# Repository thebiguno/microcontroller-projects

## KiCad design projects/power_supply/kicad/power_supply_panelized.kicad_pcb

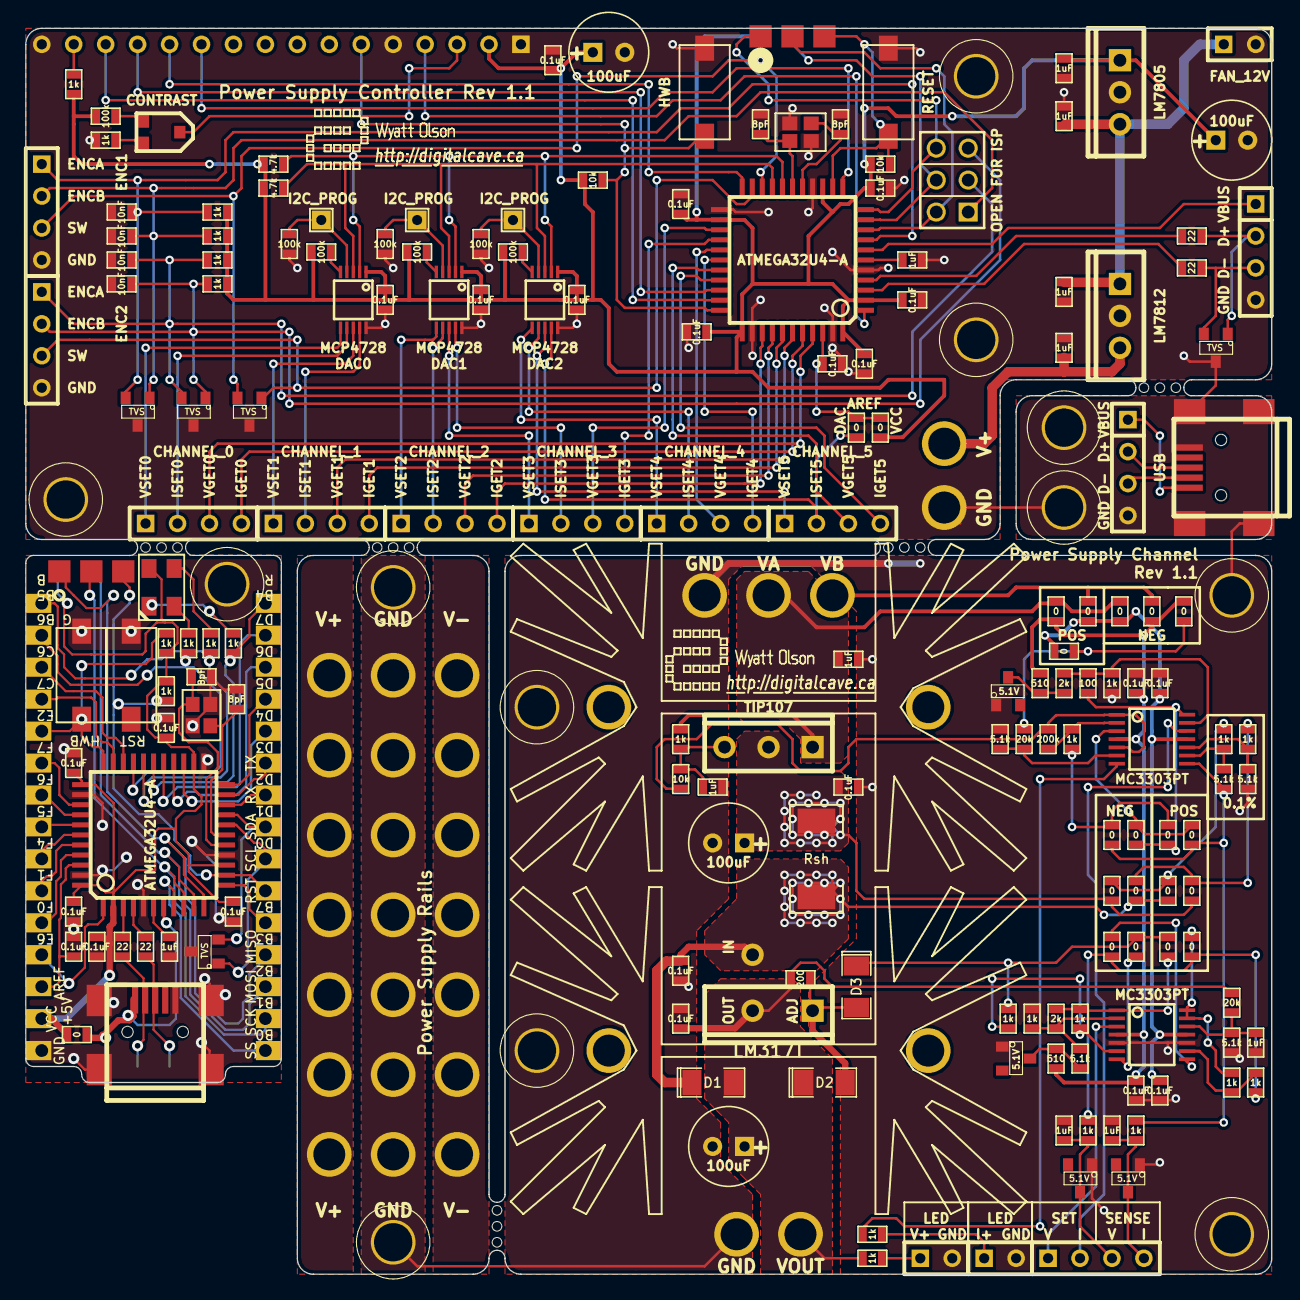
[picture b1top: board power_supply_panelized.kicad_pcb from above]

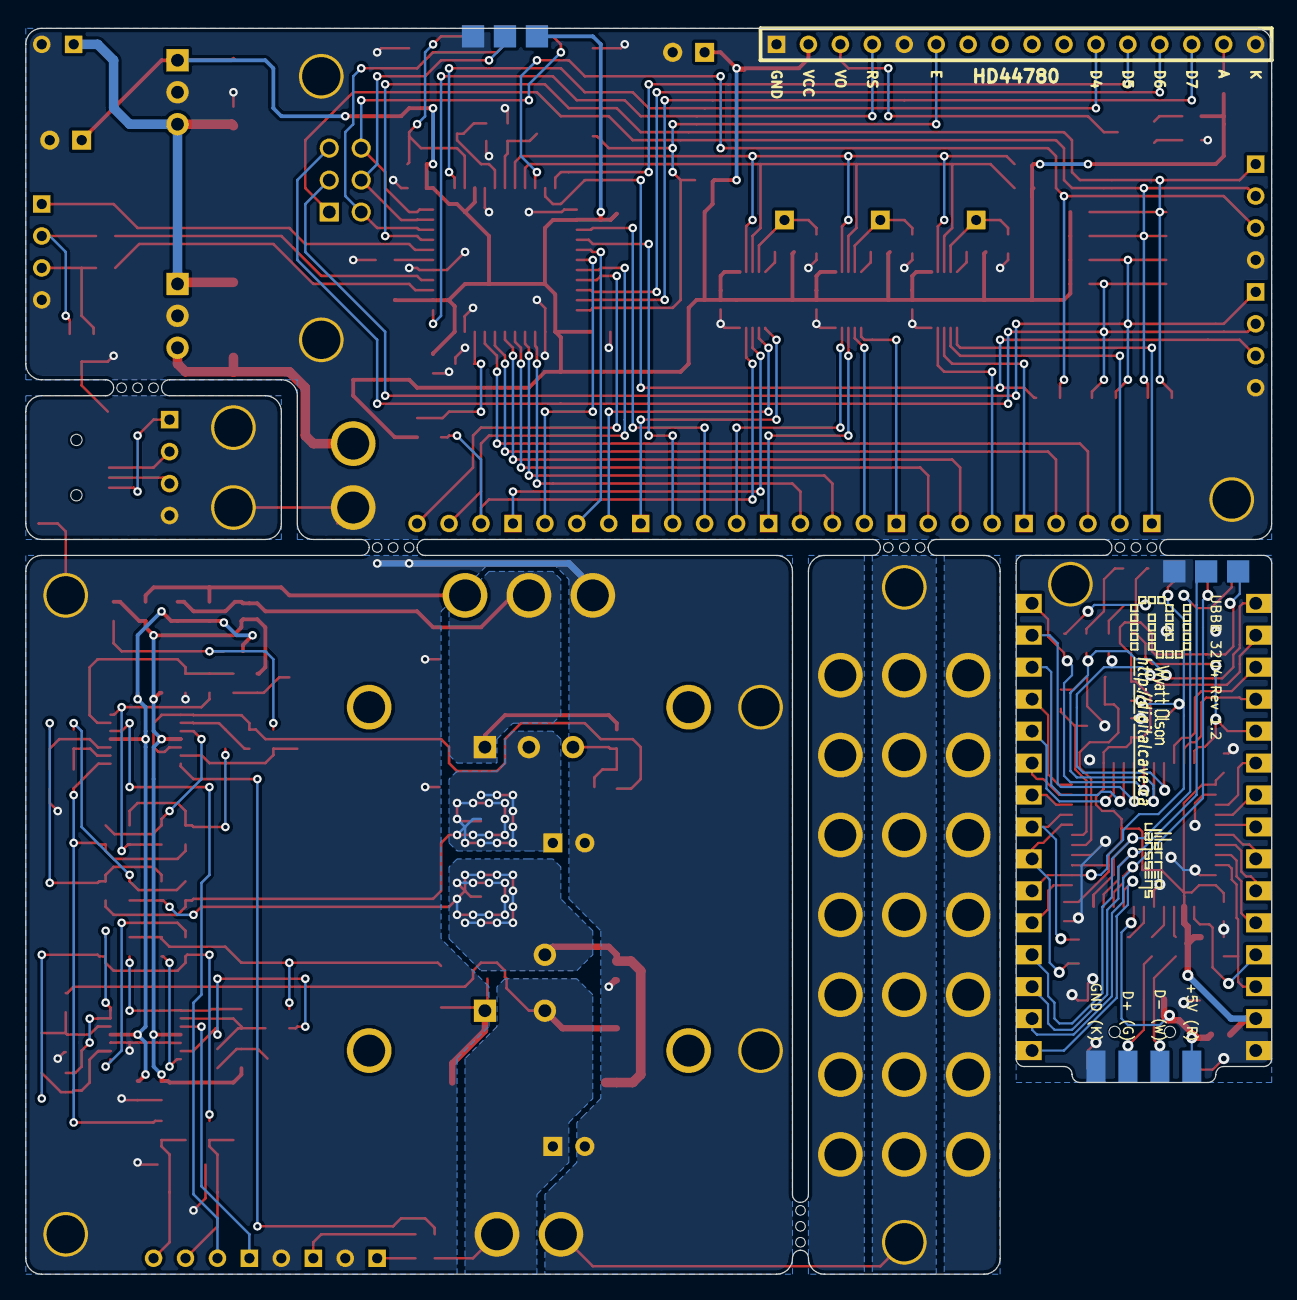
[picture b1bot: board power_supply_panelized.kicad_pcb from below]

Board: 2 copper layers, 99.1 x 99.1 mm, 223 parts (6 on the bottom side), 140 nets.

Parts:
C1, C2, C3, C4: 100uF; C1V7
C1#2, C2#2, C23, C26: 8pF; SM0603_VALUE
C3#2, C5, C5#2, C6, C6#2, C7, C7#2, C8, C8#2, C9, C9#2, C11, C12, C17, C18, C19, C20, C21, C22, C34, C35, C36, C37: 0.1uF; SM0603_VALUE
C4#2, C10, C13, C14, C15, C16, C24, C25, C31, C32, C33: 1uF; SM0603_VALUE
C27, C28, C29, C30: 10nF; SM0603_VALUE
CON1, CON1#2: USB-MINI-B; USB_MINI_B_fixed
D1, D2, D3: SCHOTTKEY; SM1206_DIODE
D1#2: RGB_LED_COMMON_ANODE_ALT1; LED_RGB_4-PLCC_ALT1
D2#2, D8, D9, D10, D11: TVS; SOT23
D4, D5, D6, D7: 5.1V; SOT23-SPECIAL
DIGITALCAVE_URL: VAL**; DIGITALCAVE_URL
DS1: HD44780; SIL-16
K1, K2, K3, K4, K5, K6, K7: VS; SCREW_TERMINAL_3
K1#2: PINS_4; PIN_ARRAY_4x1
K8: V_LED; SIL-2
K9: SUPPLY; SCREW_TERMINAL_3
K10: VOUT; SCREW_TERMINAL_2
K11: CONTROL_FEEDBACK; SIL-4
K12, K14: HEATSINK; HEATSINK_OHMITE_FSERIES
K13: I_LIM_LED; SIL-2
K15, K17: USB; SIL-4
K16: POWER; SCREW_TERMINAL_2
K18: ENC1; SIL-4
K19: ENC2; SIL-4
K20: FAN_12V; SIL-2
K21, K22, K23: I2C_PROG; SIL-1
K24: CHANNEL_0; SIL-4
K25: CHANNEL_1; SIL-4
K26: CHANNEL_2; SIL-4
K27: CHANNEL_3; SIL-4
K28: CHANNEL_4; SIL-4
K29: CHANNEL_5; SIL-4
MP1, MP1#2, MP2, MP5, MP7, MP9, MP11, MP14, MP16, MP17, MP19, MP20: MOUNTING_HOLE; MOUNTING_HOLE_#4
MP3, MP3#2, MP4, MP6, MP13: MOUSE_BITES; mouse_bites
MP8, MP15: GRAPHIC; DIGITALCAVE_AUTHOR
MP10, MP18: GRAPHIC; DIGITALCAVE_LOGO
MP12, MP21: GRAPHIC; DIGITALCAVE_URL
P1, P1#2: ISP; ISP_EDGE
P2: PROG_JMP; pin_array_3x2
P2#2, P3, P4, P5, P6, P7: CONN_5; PIN_ARRAY_5x1
Q1: TIP107; TO220_VERT
R1: Rsh; SM2512
R1#2, R2#2, R49, R52: 22; SM0603_VALUE
R2, R3, R7, R8, R8#2, R9, R15, R17, R22, R25, R26, R29, R31, R33, R37, R40, R44, R58, R59, R66, R69: 0; SM0603_VALUE
R3#2, R4, R4#2, R5, R5#2, R6#2, R7#2, R11, R12, R13, R18, R30, R32, R34, R35, R36, R38, R39, R41, R45, R47, R53, R54, R55, R56: 1k; SM0603_VALUE
R6: 200; SM0603_VALUE
R10, R67: 20k; SM0603_VALUE
R14, R19, R24, R42, R68: 5.1k; SM0603_VALUE
R16, R21: 510; SM0603_VALUE
R20, R28: 2k; SM0603_VALUE
R23: 100; SM0603_VALUE
R27, R48, R57: 10k; SM0603_VALUE
R43: 200k; SM0603_VALUE
R46, R60, R61, R62, R63, R64, R65: 100k; SM0603_VALUE
R50, R51: 4.7k; SM0603_VALUE
RV1: 10k; POTENTIOMETER_SMD
SW1: RESET; SW_6x3
SW1#2, SW2#2: SW_PUSH_SMALL; SW_6x3
SW2: HWB; SW_6x3
U1, U1#2: ATMEGA32U4-A; TQFP44
U2, U3: MC3303PT; TSSOP14
U4: LM317T; TO220_VERT
U5: LM7812; TO220_VERT
U6: LM7805; TO220_VERT
U7, U8, U9: MCP4728; MSOP10-0.5
VAL: REF; DIGITALCAVE_LOGO
VAL#2: DIGITALCAVE_AUTHOR
WJ10: VAL**; WJ10
X1, X1#2: CRYSTAL_SMD_4PIN; CRYSTAL_SMD_2.5x2

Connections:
+5V: C3.1, C4.1, C5#2.2, C6#2.2, C7#2.2, C8#2.2, C9#2.2, C17.2, C18.2, C19.2, C20.2, C21.2, C22.2, C33.1, C35.2, C36.2, C37.2, D1#2.1, DS1.2, P1.2, P1#2.2, P2#2.2, R3#2.1, R7#2.2, R8#2.2, R46.1, R47.2, R48.1, R50.2, R51.2, R53.2, R54.2, R55.2, R56.2, R57.2, R58.2, R63.1, R64.1, R65.1, U1.2, U1.14, U1.24, U1.34, U1.44, U1#2.2, U1#2.14, U1#2.24, U1#2.34, U1#2.44, U6.VO, U7.1, U8.1, U9.1
+12V: C25.1, C32.1, K20.1, U5.VO, U6.VI
/AREF: C3#2.1, C34.2, P2#2.3, R58.1, R59.1, U1.42, U1#2.42
/B0: P7.5, U1#2.8
/B1: P1#2.3, P7.4, U1#2.9
/B2: P1#2.4, P7.3, U1#2.10
/B3: P1#2.1, P7.2, U1#2.11
/B4: P5.1, R4#2.2, U1#2.28
/B5: P4.5, R5#2.2, U1#2.29
/B6: P4.4, R6#2.2, U1#2.30
/B7: P7.1, U1#2.12
/C6: P4.3, U1#2.31
/C7: P4.2, U1#2.32
/CONT_PWR_IN: C24.1, K16.2, U5.VI
/D0: D2#2.1, P6.4, U1#2.18
/D1: D2#2.2, P6.3, U1#2.19
/D2: P6.2, U1#2.20
/D3: P6.1, U1#2.21
/D4: DS1.11, P5.5, U1.12, U1#2.25
/D5: DS1.12, P5.4, U1.22, U1#2.22
/D6: DS1.13, P5.3, U1.31, U1#2.26
/D7: DS1.14, P5.2, U1.32, U1#2.27
/D+: CON1#2.3, K1#2.2, R1#2.1
/D-: CON1#2.2, K1#2.3, R2#2.1
/E: DS1.6, R57.1, SW2.1, U1.33
/E2: P4.1, R7#2.1, SW2#2.1, U1#2.33
/E6: P2#2.4, U1#2.1
/ENC1_A: C28.2, D9.2, K18.1, R54.1, U1.8
/ENC1_B: C27.2, D9.1, K18.2, P2.1, R53.1
/ENC1_SW: D8.2, K18.3, U1.20
/ENC2_A: C30.2, D10.2, K19.1, P2.3, R56.1
/ENC2_B: C29.2, D10.1, K19.2, P2.5, R55.1
/ENC2_SW: D8.1, K19.3, U1.21
/F0: P2#2.5, U1#2.41
/F1: P3.1, U1#2.40
/F4: P3.2, U1#2.39
/F5: P3.3, U1#2.38
/F6: P3.4, U1#2.37
/F7: P3.5, U1#2.36
/I_DIFF: R19.1, R22.2, R30.1, R31.1, U2.8
/I_GET: C16.1, D7.2, K11.4, R30.2
/I_GET0: K24.4, U1.40
/I_GET1: K25.4, U1.38
/I_GET2: K26.4, U1.36
/I_GET3: K27.4, U1.26
/I_GET4: K28.4, U1.28
/I_GET5: K29.4, U1.30
/I_LIM: C13.1, Q1.B, R5.2, R27.1
/I_LIM_LED: R27.2, R43.2, U2.1, U2.5
/I_SET: K11.2, U2.12
/I_SET0: K24.2, U7.7
/I_SET1: K25.2, U7.9
/I_SET2: K26.2, U8.7
/I_SET3: K27.2, U8.9
/I_SET4: K28.2, U9.7
/I_SET5: K29.2, R59.2, U9.9
/I_SET_BIAS: R23.2, R26.1, R37.2, U2.14
/LB: D1#2.3, R5#2.1
/LG: D1#2.4, R6#2.1
/LR: D1#2.2, R4#2.1
/MISO: P1.1, P2.6, U1.11
/MOSI: P1.4, P2.4, U1.10
/POST_CS: C12.1, D1.2, R1.2, R25.1, R33.2, U4.3
/PRE_CS: C1.1, C11.2, Q1.C, R1.1, R17.1, R40.2
/RAIL_V+: K1.1, K2.1, K3.1, K4.1, K5.1, K6.1, K7.1
/RAIL_V-: K1.3, K2.3, K3.3, K4.3, K5.3, K6.3, K7.3
/RESET: P1.5, P1#2.5, P6.5, R3#2.2, R48.2, SW1.2, SW1#2.2, U1.13, U1#2.13
/RS: DS1.4, U1.1
/SCK: P1.3, P2.2, U1.9
/SCL: R51.1, U1.18, U7.2, U8.2, U9.2
/SDA: R50.1, U1.19, U7.3, U8.3, U9.3
/UCAP: C4#2.1, C31.2, U1.6, U1#2.6
/V+: C5.2, C7.2, R2.2, R3.2, R16.1, R21.1, R66.1, U2.4, U3.4
/V-: C6.2, C8.2, R7.2, R8.2, R69.2, U2.11, U3.11
/VA: C10.1, K9.2, Q1.E, R3.1, R5.1, R8.1
/VADJ: D3.2, R29.1, R39.1, R44.2
/VB: K9.3, R2.1, R7.1
/VBUS: CON1#2.1, K1#2.4, K17.1, R8#2.1, U1.7, U1#2.7
/V_GET: C15.1, D4.2, K11.3, R13.1
/V_GET0: K24.3, U1.41
/V_GET1: K25.3, U1.39
/V_GET2: K26.3, U1.37
/V_GET3: K27.3, U1.25
/V_GET4: K28.3, U1.27
/V_GET5: K29.3, U1.29
/V_OUT: C2.1, C9.2, D1.1, D2.2, K10.2, R4.2, R6.2, R10.2, U4.2
/V_SET: K11.1, U3.3
/V_SET0: K24.1, U7.6
/V_SET1: K25.1, U7.8
/V_SET2: K26.1, U8.6
/V_SET3: K27.1, U8.8
/V_SET4: K28.1, U9.6
/V_SET5: K29.1, U9.8
GND: C1.2, C1#2.1, C2.2, C2#2.1, C3.2, C3#2.2, C4.2, C4#2.2, C5.1, C5#2.1, C6.1, C6#2.1, C7.1, C7#2.1, C8.1, C8#2.1, C9.1, C9#2.1, C10.2, C11.1, C12.2, C13.2, C14.2, C15.2, C16.2, C17.1, C18.1, C19.1, C20.1, C21.1, C22.1, C23.1, C24.2, C25.2, C26.1, C27.1, C28.1, C29.1, C30.1, C31.1, C32.2, C33.2, C34.1, C35.1, C36.1, C37.1, CON1.5, CON1.6, CON1.7, CON1.8, CON1.9, CON1#2.5, CON1#2.6, CON1#2.7, CON1#2.8, CON1#2.9, D2#2.3, D4.1, D5.1, D6.1, D7.1, D8.3, D9.3, D10.3, D11.3, DS1.1, DS1.5, DS1.16, K1.2, K1#2.1, K2.2, K3.2, K4.2, K5.2, K6.2, K7.2, K8.2, K9.1, K10.1, K13.2, K15.4, K16.1, K17.4, K18.4, K19.4, K20.2, MP1.1, MP1#2.1, MP2.1, MP5.1, MP7.1, MP9.1, MP11.1, MP14.1, MP16.1, MP17.1, MP19.1, MP20.1, P1.6, P1#2.6, P2#2.1, R14.1, R35.1, R36.1, R42.1, R45.2, R60.2, R61.2, R62.2, R68.2, SW1.1, SW1#2.1, SW2.2, SW2#2.2, U1.5, U1.15, U1.23, U1.35, U1.43, U1#2.5, U1#2.15, U1#2.23, U1#2.35, U1#2.43, U3.5, U3.10, U5.GND, U6.GND, U7.10, U8.10, U9.10, X1.2, X1.4, X1#2.2, X1#2.4
unnamed: C26.2, U1.16, X1.3
unnamed: C23.2, U1.17, X1.1
unnamed: R67.2, R68.1, U2.6
unnamed: R52.2, U1.3
unnamed: R49.2, U1.4
unnamed: DS1.15, R47.1
unnamed: R22.1, R26.2, U2.3
unnamed: R28.2, R38.1, R44.1, U3.1
unnamed: R29.2, U3.7
unnamed: R45.1, RV1.1
unnamed: R46.2, RV1.2
unnamed: R15.2, U3.8
unnamed: R9.1, R11.1, R13.2, R15.1
unnamed: R31.2, R32.1, R37.1
unnamed: K13.1, R34.2
unnamed: R34.1, U2.7
unnamed: D6.2, R21.2, R24.2
unnamed: CON1.1, K15.1
unnamed: DS1.3, RV1.3
unnamed: C2#2.2, R41.2, R42.2, U1#2.16, U2.10, X1#2.1
unnamed: C1#2.2, R18.1, R19.2, U1#2.17, U2.9, X1#2.3
unnamed: R17.2, R18.2, R25.2
unnamed: R33.1, R40.1, R41.1
unnamed: R1#2.2, U1#2.4
unnamed: R2#2.2, U1#2.3
unnamed: R20.1, R23.1, R35.2, U2.13
unnamed: D5.2, R16.2, R20.2
unnamed: R66.2, R67.1, R69.1
unnamed: K8.1, R4.1
unnamed: K23.1, R62.1, U9.4
unnamed: K22.1, R61.1, U8.4
unnamed: K21.1, R60.1, U7.4
unnamed: D11.2, K17.3, R52.1
unnamed: D11.1, K17.2, R49.1
unnamed: CON1.2, K15.3
unnamed: CON1.3, K15.2
unnamed: R24.1, R28.1, R36.2, U3.2
unnamed: R11.2, R12.1, U3.9
unnamed: R9.2, R12.2, U3.13, U3.14
unnamed: D2.1, D3.1, R6.1, U4.1
unnamed: R38.2, R39.2, U3.6
unnamed: C14.1, R10.1, R14.2, U3.12
unnamed: R32.2, R43.1, U2.2
unnamed: R64.2, U8.5
unnamed: R63.2, U7.5
unnamed: R65.2, U9.5

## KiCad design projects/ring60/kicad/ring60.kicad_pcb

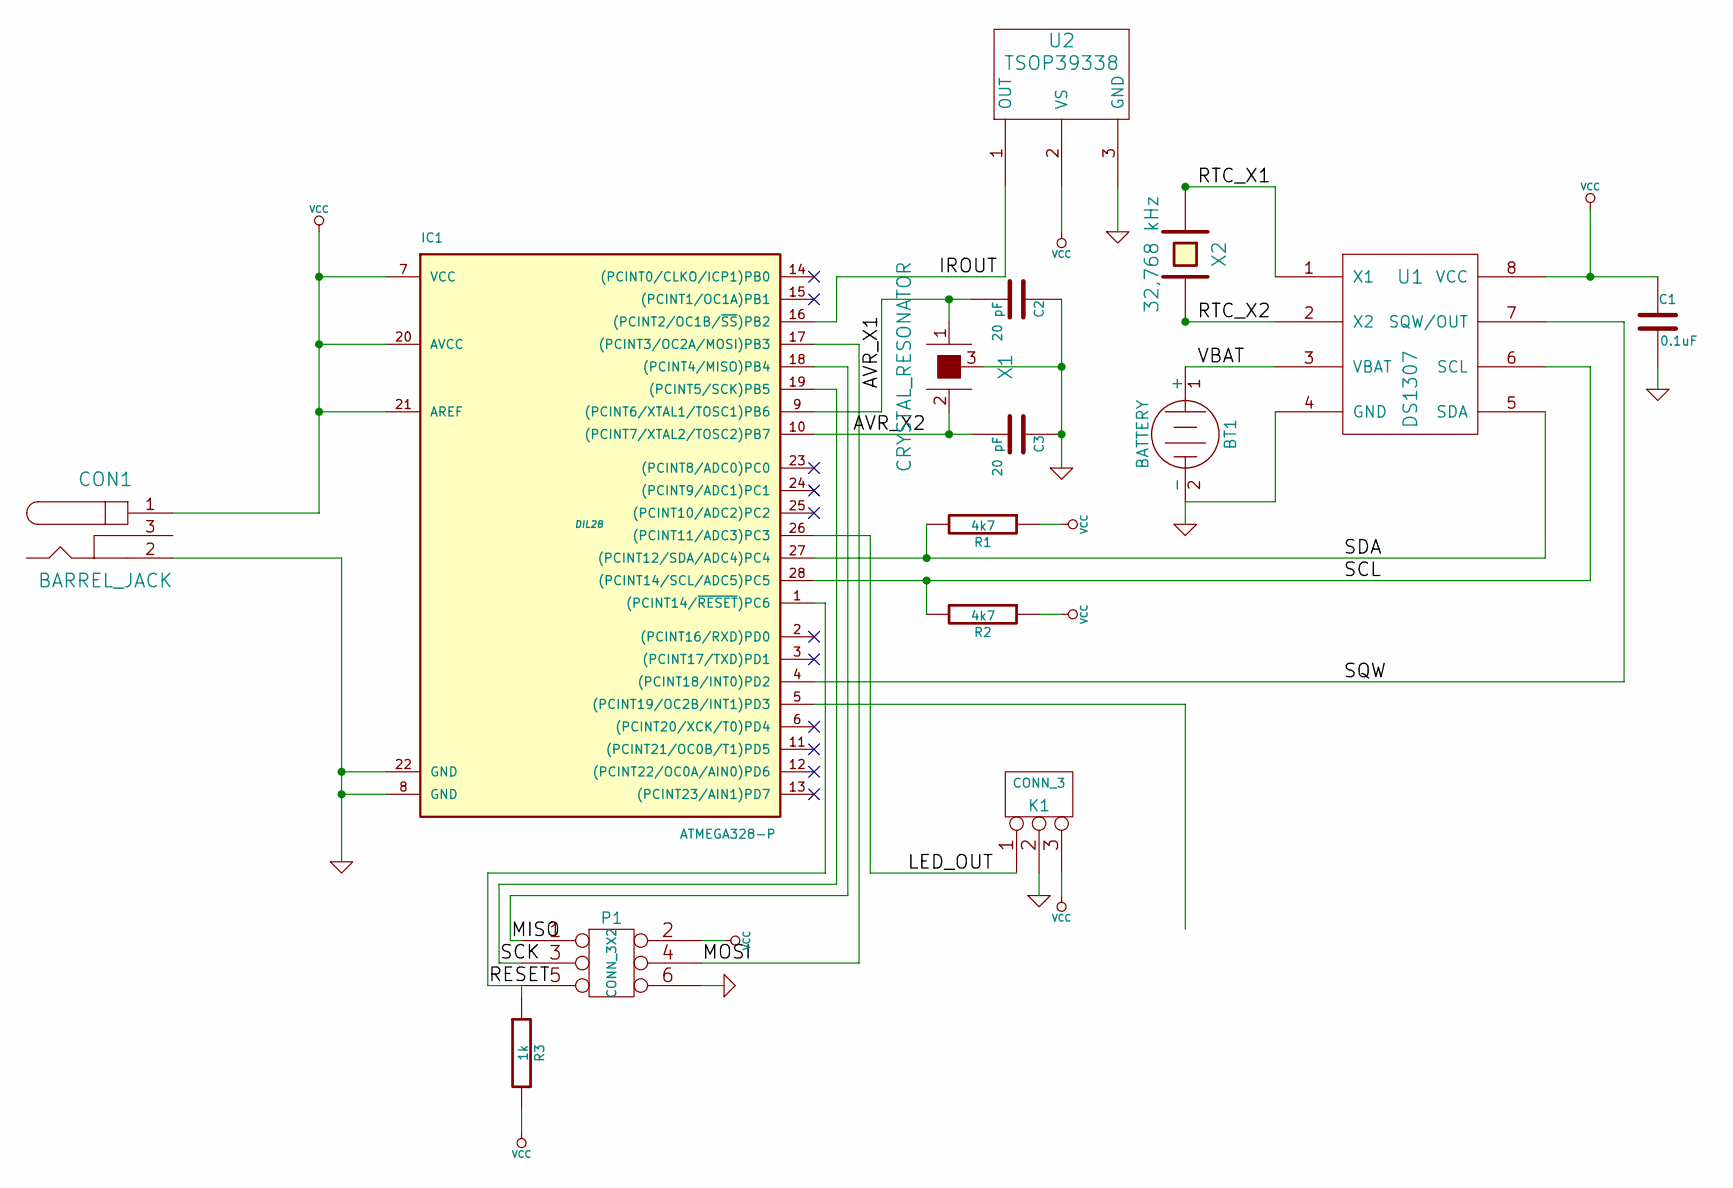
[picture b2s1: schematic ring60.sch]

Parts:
BT1: BATTERY
C1: 0.1uF
C2, C3: 20 pF
CON1: BARREL_JACK
IC1: ATMEGA328-P; DIL28
K1: CONN_3
P1: CONN_3X2
R1, R2: 4k7
R3: 1k
U1: DS1307
U2: TSOP39338
X1: CRYSTAL_RESONATOR
X2: 32,768 kHz

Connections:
/AVR_X1: C2.2, IC1.9 ((PCINT6/XTAL1/TOSC1)PB6), X1.1 (XTAL1)
/AVR_X2: C3.2, IC1.10 ((PCINT7/XTAL2/TOSC2)PB7), X1.2 (XTAL2)
/IROUT: IC1.16 ((PCINT2/OC1B/~SS~)PB2), U2.1 (OUT)
/LED_OUT: IC1.26 ((PCINT11/ADC3)PC3), K1.1
/MISO: IC1.18 ((PCINT4/MISO)PB4), P1.1
/MOSI: IC1.17 ((PCINT3/OC2A/MOSI)PB3), P1.4
/RESET: IC1.1 ((PCINT14/~RESET~)PC6), P1.5, R3.1
/RTC_X1: U1.1 (X1), X2.1
/RTC_X2: U1.2 (X2), X2.2
/SCK: IC1.19 ((PCINT5/SCK)PB5), P1.3
/SCL: IC1.28 ((PCINT14/SCL/ADC5)PC5), R2.2, U1.6 (SCL)
/SDA: IC1.27 ((PCINT12/SDA/ADC4)PC4), R1.2, U1.5 (SDA)
/SQW: IC1.4 ((PCINT18/INT0)PD2), U1.7 (SQW/OUT)
/VBAT: BT1.1 (+), U1.3 (VBAT)
GND: BT1.2 (-), C1.2, C2.1, C3.1, CON1.2, IC1.8 (GND), IC1.22 (GND), K1.2 (PM), P1.6, U1.4 (GND), U2.3 (GND), X1.3 (GND); also elsewhere on the board
VCC: C1.1, CON1.1, IC1.7 (VCC), IC1.20 (AVCC), IC1.21 (AREF), K1.3, P1.2, R1.1, R2.1, R3.2, U1.8 (VCC), U2.2 (VS)

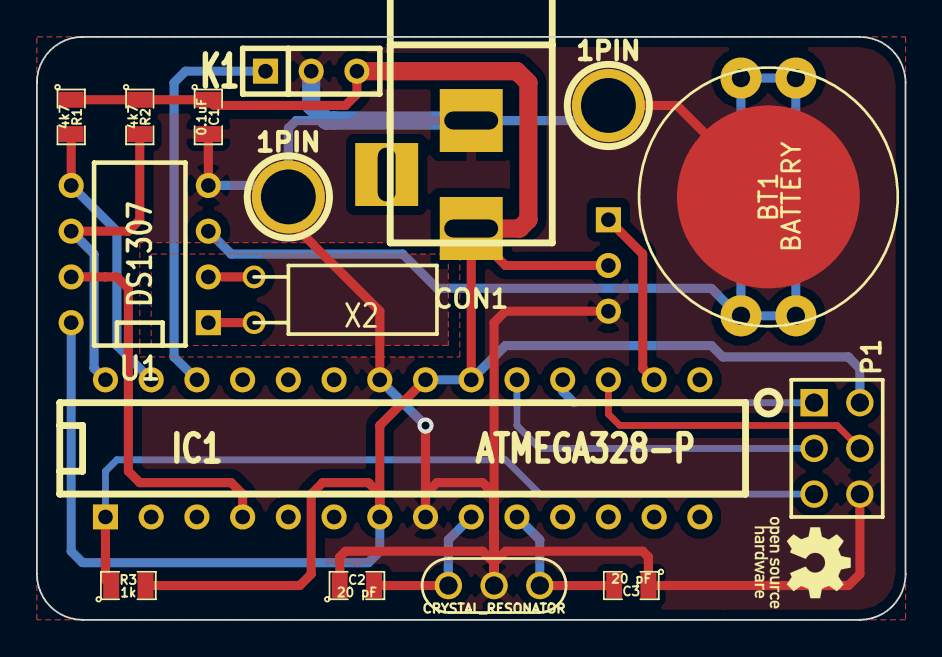
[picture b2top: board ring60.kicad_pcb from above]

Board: 2 copper layers, 48.3 x 32.4 mm, 18 parts (1 on the bottom side), 16 nets.

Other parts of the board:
1PIN, 1PIN#2: P***; 1pin
VAL: REF; Open_Source_Hardware_Logo

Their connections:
GND: 1PIN.1, 1PIN#2.1; also elsewhere on the board

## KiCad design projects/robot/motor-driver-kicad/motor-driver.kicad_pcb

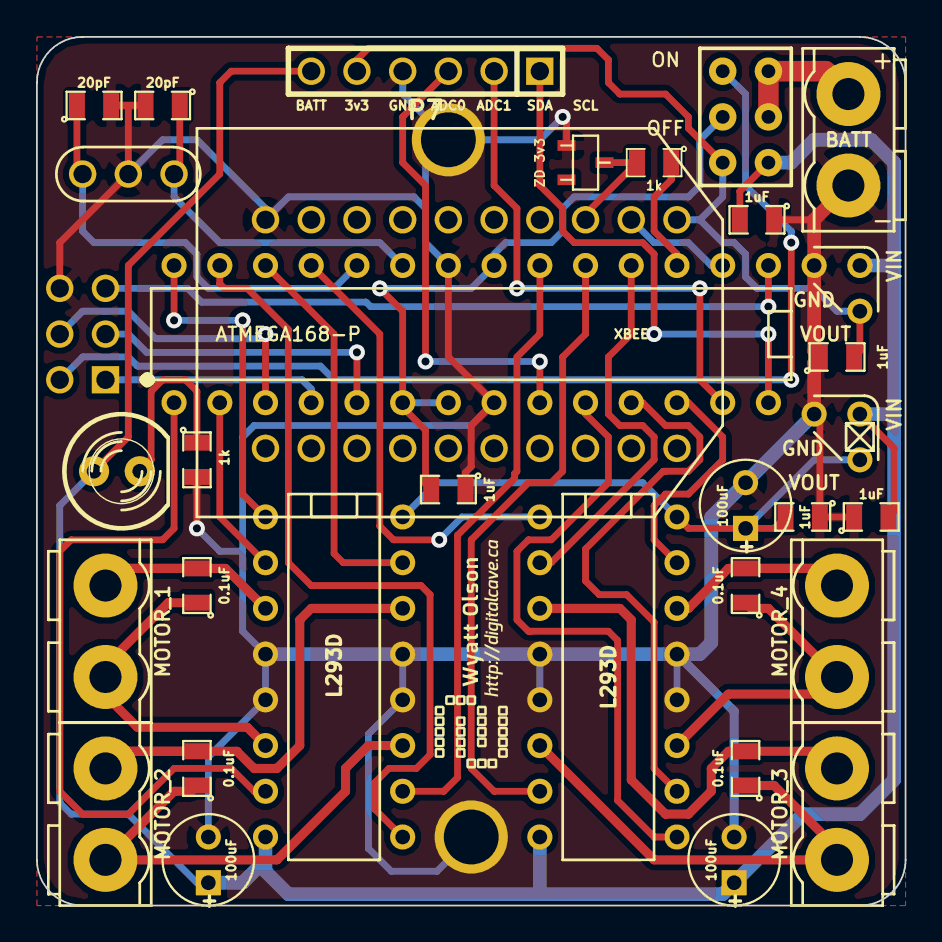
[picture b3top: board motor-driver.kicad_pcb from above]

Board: 2 copper layers, 48.3 x 48.3 mm, 36 parts (0 on the bottom side), 40 nets.

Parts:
1PIN, 1PIN#2: P***; 1pin
C1, C2, C3, C4, C17: 1uF; SM0805
C5, C6: 20pF; SM0805
C7, C8, C9, C12: 0.1uF; SM0805
C10, C15, C16: 100uF; C1V5
D1: ZD 3v3; sot23
D2: LED; LED-5MM
IC1: ATMEGA168-P; DIP-28__300
P1: BATT; SCREW_TERMINAL_2
P2: ISP
P3: MOTOR_1; SCREW_TERMINAL_2
P4: MOTOR_2; SCREW_TERMINAL_2
P5: MOTOR_3; SCREW_TERMINAL_2
P6: MOTOR_4; SCREW_TERMINAL_2
P7: CONN_6; PIN_ARRAY-6X1
R1, R2: 1k; SM0805
S1: DPDT
U1, U2: L293D; DIP-16__300
VAL: DIGITALCAVE_LOGO_WIDE_SMALL
VR1, VR2: MCP1702; TO92_SMALL
X1: CRYSTAL_RESONATOR
X2: XBEE; XBEE_SPARKFUN_BREAKOUT

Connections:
+3.3V: C4.2, P7.5, S1.6, VR2.3, X2.1
+5V: C2.2, C16.1, U1.16, U2.16, VR1.3
+BATT: C1.2, C3.2, C10.1, C15.1, D2.1, P7.6, S1.3, U1.8, U2.8, VR1.2, VR2.2
/ADC0: IC1.23, P7.3
/AVR_VCC: C17.2, IC1.7, IC1.20, IC1.21, S1.5
/BATTERY: P1.2, S1.1, S1.2
/MISO: IC1.18, P2.1
/MOSI: IC1.17, P2.4
/MOTOR1_1A: IC1.16, U1.2
/MOTOR1_1Y: C12.2, P3.1, U1.3
/MOTOR1_2A: IC1.15, U1.7
/MOTOR1_2Y: C12.1, P3.2, U1.6
/MOTOR1_ENABLE: IC1.14, U1.1
/MOTOR2_3A: IC1.6, U1.10
/MOTOR2_3Y: C8.1, P4.2, U1.11
/MOTOR2_4A: IC1.12, U1.15
/MOTOR2_4Y: C8.2, P4.1, U1.14
/MOTOR2_ENABLE: IC1.13, U1.9
/MOTOR3_1A: IC1.4, U2.2
/MOTOR3_1Y: C7.2, P5.2, U2.3
/MOTOR3_2A: IC1.5, U2.7
/MOTOR3_2Y: C7.1, P5.1, U2.6
/MOTOR3_ENABLE: IC1.11, U2.1
/MOTOR4_3A: IC1.25, U2.10
/MOTOR4_3Y: C9.1, P6.1, U2.11
/MOTOR4_4A: IC1.26, U2.15
/MOTOR4_4Y: C9.2, P6.2, U2.14
/MOTOR4_ENABLE: IC1.24, U2.9
/PROG_VCC: P2.2, S1.4
/RESET: IC1.1, P2.5
/RX: IC1.2, X2.2
/SCK: IC1.19, P2.3
/SCL: IC1.28, P7.1
/SDA: IC1.27, P7.2
/TX: IC1.3, R1.1
/XTAL1: C5.1, IC1.9, X1.1
/XTAL2: C6.1, IC1.10, X1.2
GND: 1PIN.1, 1PIN#2.1, C1.1, C2.1, C3.1, C4.1, C5.2, C6.2, C10.2, C15.2, C16.2, C17.1, D1.1, IC1.8, IC1.22, P1.1, P2.6, P7.4, R2.2, U1.4, U1.5, U1.12, U1.13, U2.4, U2.5, U2.12, U2.13, VR1.1, VR2.1, X1.3, X2.10
unnamed: D1.2, R1.2, X2.3
unnamed: D2.2, R2.1

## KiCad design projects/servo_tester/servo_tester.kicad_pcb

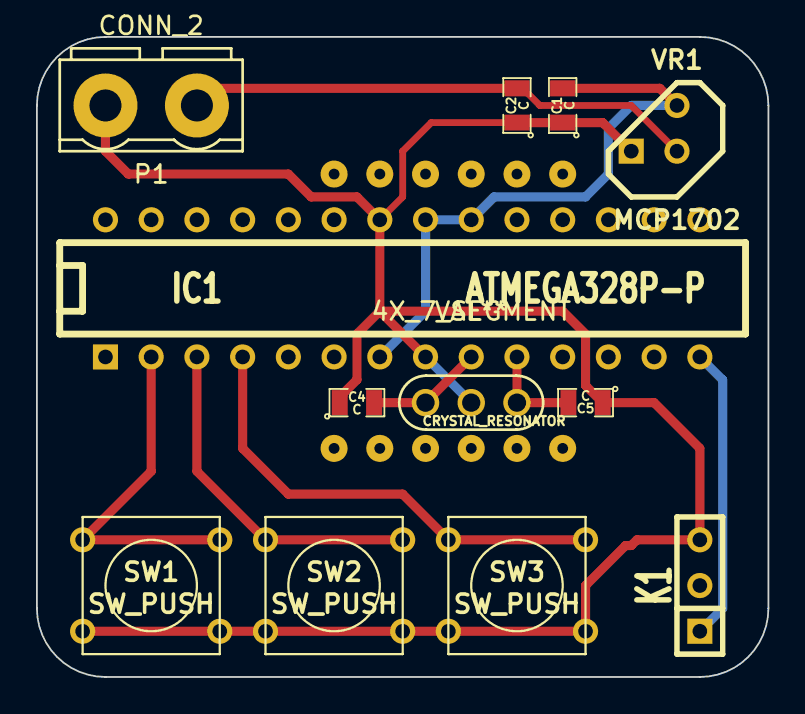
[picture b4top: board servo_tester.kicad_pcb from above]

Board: 2 copper layers, 40.6 x 35.6 mm, 13 parts (0 on the bottom side), 9 nets.

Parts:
4X_7_SEGMENT: VAL**; 4X_7_SEGMENT
C1, C2, C4, C5: C; SM0805
IC1: ATMEGA328P-P; DIP-28__300
K1: CONN_3; SIL-3
P1: CONN_2; SCREW_TERMINAL_2
SW1, SW2, SW3: SW_PUSH; SW_PUSH_SMALL
VR1: MCP1702; TO92
X1: CRYSTAL_RESONATOR

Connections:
+5V: C1.2, IC1.7, IC1.20, IC1.21, K1.2, VR1.3
GND: C1.1, C2.1, C4.1, C5.1, IC1.8, IC1.22, K1.3, P1.2, SW1.2, SW2.2, SW3.2, VR1.1, X1.3
unnamed: C5.2, IC1.10, X1.1
unnamed: C4.2, IC1.9, X1.2
unnamed: IC1.2, SW1.1
unnamed: IC1.3, SW2.1
unnamed: IC1.14, K1.1
unnamed: IC1.4, SW3.1
unnamed: C2.2, P1.1, VR1.2

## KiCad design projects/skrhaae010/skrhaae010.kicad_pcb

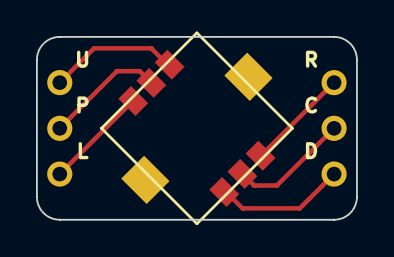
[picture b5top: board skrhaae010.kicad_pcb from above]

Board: 2 copper layers, 17.8 x 10.2 mm, 3 parts (0 on the bottom side), 6 nets.

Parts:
K1, K2: CONN_3; SIL-3
P1: CONN_6; skrhaae010

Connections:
unnamed: K1.1, P1.1
unnamed: K1.2, P1.2
unnamed: K1.3, P1.3
unnamed: K2.1, P1.4
unnamed: K2.2, P1.5
unnamed: K2.3, P1.6

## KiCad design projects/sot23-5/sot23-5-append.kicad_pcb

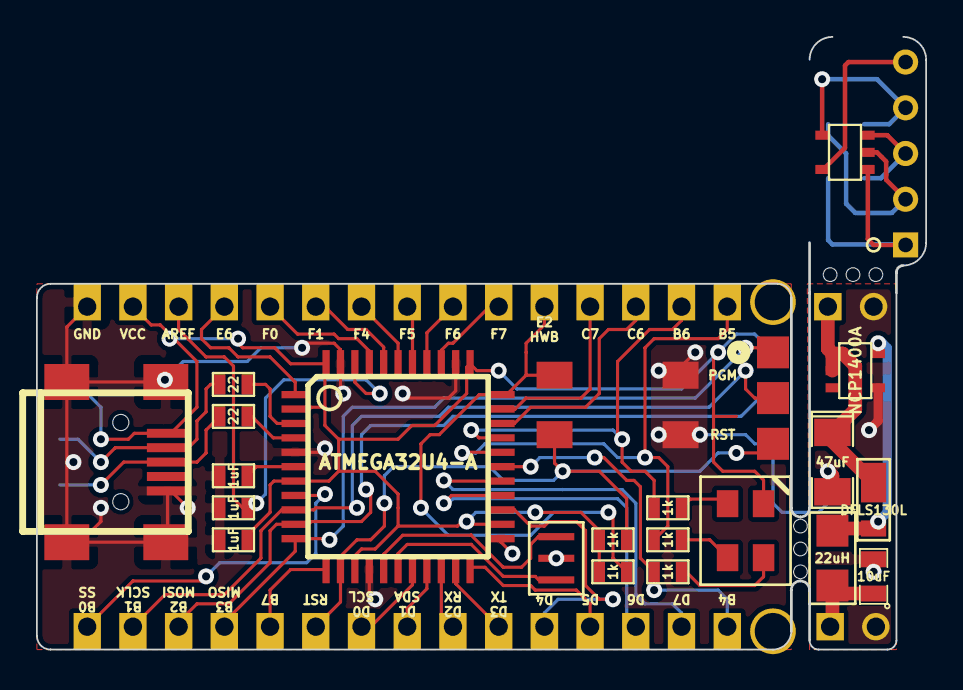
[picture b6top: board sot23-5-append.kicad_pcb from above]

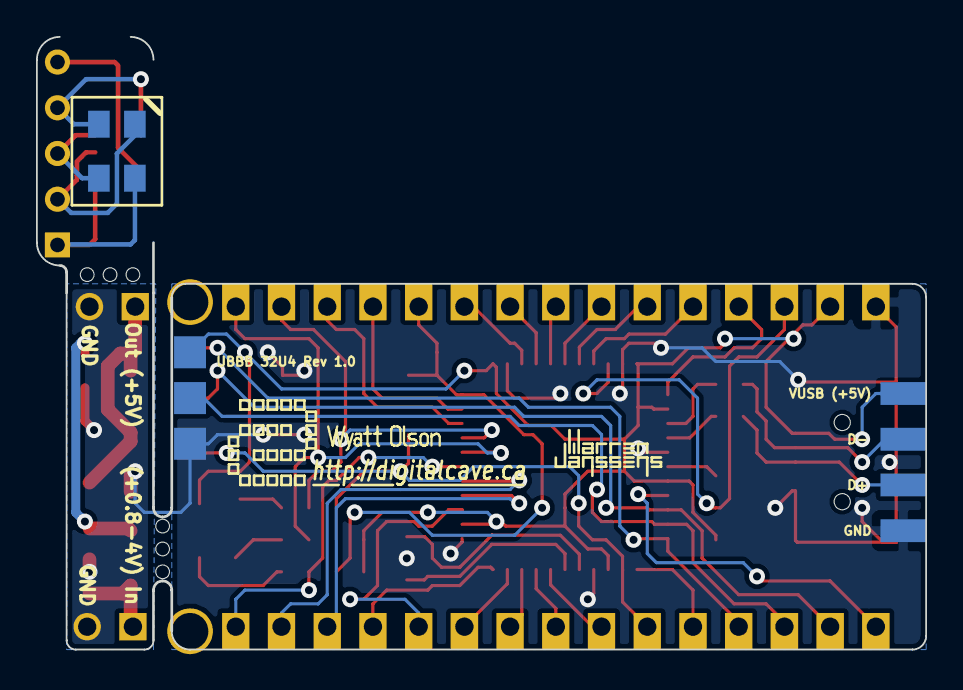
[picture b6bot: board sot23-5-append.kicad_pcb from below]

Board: 2 copper layers, 49.4 x 34.0 mm, 42 parts (6 on the bottom side), 47 nets.

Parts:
1PIN, 1PIN#2: P***; 1pin
C1: 10uF; SM0805
C2: 47uF; SM1206POL
C3, C4, C5: 1uF; SM0603_VALUE
CON1: USB-MINI-B; USB_MINI_B_fixed
D1: DFLS130L; POWERDI_123
D1#2: RGB_LED_COMMON_ANODE_ALT1; LED_RGB_4-PLCC_ALT1
D2: RGB_LED_COMMON_ANODE; LED_RGB_4-PLCC_ALT1
DIGITALCAVE_URL: VAL**; DIGITALCAVE_URL
L1: 22uH; SM1007
P1: ISP; ISP_EDGE
P1#2, P2#2: CONN_2; PIN_ARRAY_2X1
P1#3: CONN_5; SIL-5
P2, P3, P4, P5, P6, P7: CONN_5; PIN_ARRAY_5x1
PIN_ARRAY_4X1: Val**; PIN_ARRAY_4x1
R2, R3: 22; SM0603_VALUE
R4, R5, R6, R7, R8: 1k; SM0603_VALUE
SW1, SW2: SW_PUSH_SMALL; SW_6x3
U1: ATMEGA32U4-A; TQFP44
VAL: REF; DIGITALCAVE_LOGO
VAL#2: DIGITALCAVE_AUTHOR
VR1, VR1#2: NCP1400A; SOT23-5
WJ10: VAL**; WJ10
X1: RESONATOR; RESONATOR_SMD-3
mouse_bites: VAL**; mouse_bites
mouse_bites#2: VAL**; mouse_bites

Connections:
+5V: C5.1, CON1.1, D2.2, P1.2, P2.2, PIN_ARRAY_4X1.4, R4.1, R6.2, U1.2, U1.7, U1.14, U1.24, U1.34, U1.44
/AREF: C3.2, P2.3, U1.42
/B0: P7.5, U1.8
/B1: P1.3, P7.4, U1.9
/B2: P1.4, P7.3, U1.10
/B3: P1.1, P7.2, U1.11
/B4: P5.1, R5.2, U1.28
/B5: P4.5, R7.2, U1.29
/B6: P4.4, R8.2, U1.30
/B7: P7.1, U1.12
/C6: P4.3, U1.31
/C7: P4.2, U1.32
/D0: P6.4, U1.18
/D1: P6.3, U1.19
/D2: P6.2, U1.20
/D3: P6.1, U1.21
/D4: P5.5, U1.25
/D5: P5.4, U1.22
/D6: P5.3, U1.26
/D7: P5.2, U1.27
/D+: CON1.3, PIN_ARRAY_4X1.2, R2.1
/D-: CON1.2, PIN_ARRAY_4X1.3, R3.1
/E2: P4.1, R6.1, SW2.1, U1.33
/E6: P2.4, U1.1
/F0: P2.5, U1.41
/F1: P3.1, U1.40
/F4: P3.2, U1.39
/F5: P3.3, U1.38
/F6: P3.4, U1.37
/F7: P3.5, U1.36
/RESET: P1.5, P6.5, R4.2, SW1.2, U1.13
GND: C1.2, C2.2, C3.1, C4.1, C5.2, CON1.5, CON1.6, CON1.7, CON1.8, CON1.9, P1.6, P1#2.2, P2.1, P2#2.2, PIN_ARRAY_4X1.1, SW1.1, SW2.2, U1.5, U1.15, U1.23, U1.35, U1.43, VR1.4, X1.2
unnamed: D1#2.1, P1#3.1, VR1#2.1
unnamed: D1#2.3, P1#3.3, VR1#2.3
unnamed: D1#2.4, P1#3.4, VR1#2.4
unnamed: P1#3.5, VR1#2.5
unnamed: D1.1, D1#2.2, L1.2, P1#3.2, VR1.5, VR1#2.2
unnamed: C2.1, D1.2, P2#2.1, VR1.1, VR1.2
unnamed: C1.1, L1.1, P1#2.1
unnamed: D2.4, R8.1
unnamed: D2.3, R7.1
unnamed: D2.1, R5.1
unnamed: U1.16, X1.3
unnamed: U1.17, X1.1
unnamed: R2.2, U1.4
unnamed: R3.2, U1.3
unnamed: C4.2, U1.6

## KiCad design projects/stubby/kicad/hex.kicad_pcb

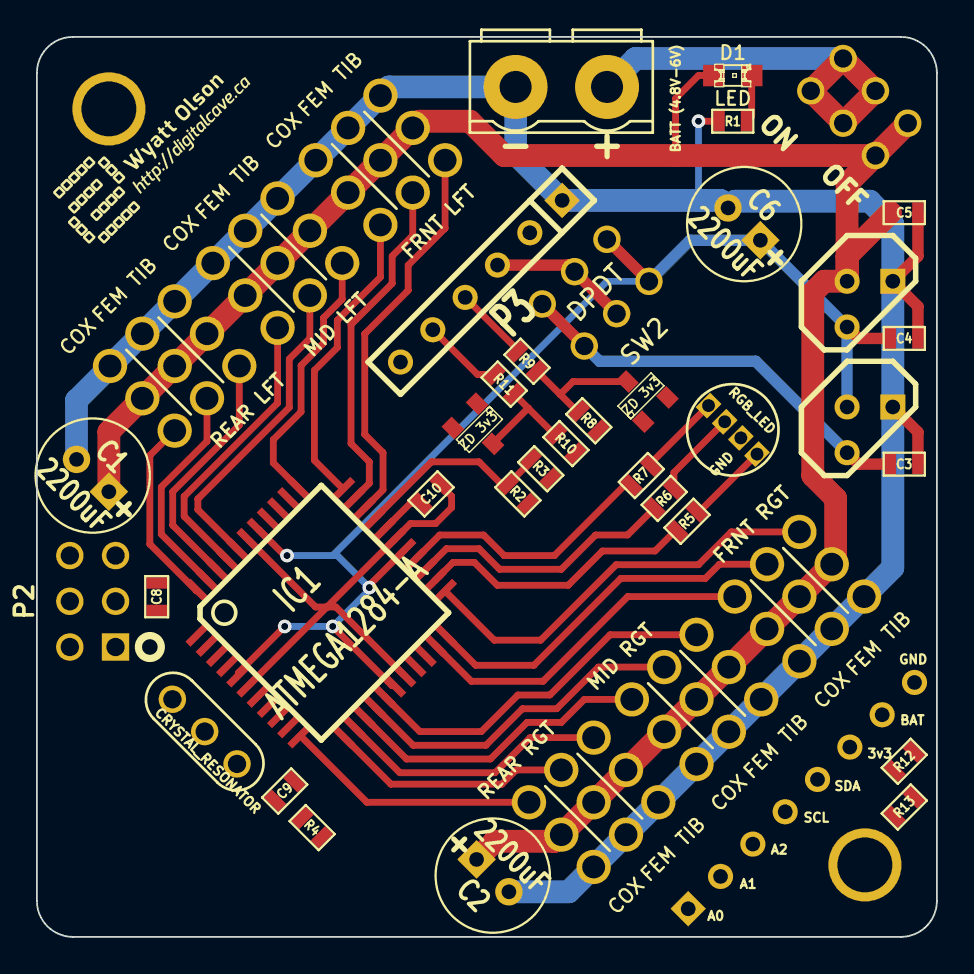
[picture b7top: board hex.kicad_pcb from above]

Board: 2 copper layers, 50.0 x 50.0 mm, 45 parts (0 on the bottom side), 50 nets.

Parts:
1PIN, 1PIN#2: P***; 1pin
C1, C2, C6: 2200uF; C1V7
C3, C4, C5, C10: 1uF; SM0603
C8, C9: 20pF; SM0603
D1: LED; LED-0805
D2: RGB_LED; LED_RGB
IC1: ATMEGA1284-A; TQFP44
P1: BATT (4.8V-6V); SCREW_TERMINAL_2
P2: PROG; ISP
P3: CONN_6; SIL-6
P4: CONN_8; SIL-8
R1, R2, R3, R4, R5, R6, R7, R8, R9, R10, R11, R12, R13: 1k; SM0603
S1: FRNT LFT; HEX_LEG
S2: FRNT RGT; HEX_LEG_REVERSE
S3: MID LFT; HEX_LEG
S4: MID RGT; HEX_LEG_REVERSE
S5: REAR LFT; HEX_LEG
S6: REAR RGT; HEX_LEG_REVERSE
SW1: DPDT
SW2: DPDT; DPDT_Wide
VAL: DIGITALCAVE_LOGO_WIDE_SMALL
VR1, VR2: MCP1702; TO92
X1: CRYSTAL_RESONATOR
ZD1, ZD2: ZD 3v3; SOT23

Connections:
+3.3V: C3.1, P4.6, R12.1, R13.1, SW2.3, SW2.6, VR2.3
+5V: C4.1, C6.1, IC1.5, IC1.17, IC1.27, IC1.38, P2.2, P4.7, R4.1, SW2.1, SW2.4, VR1.3, VR2.2
/ADC0: IC1.37, P4.1
/ADC1: IC1.36, P4.2
/ADC2: IC1.35, P4.3
/ADC_BATTERY_METER: IC1.30, R2.2, R3.2
/AREF: C10.2, IC1.29
/AVR_RX: R8.2, R9.1, ZD1.2
/AVR_TX: R10.2, R11.1, ZD2.2
/I2C_SCL: IC1.19, P4.4, R13.2
/I2C_SDA: IC1.20, P4.5, R12.2
/LED_BL: IC1.25, R6.1
/LED_BL_R: D2.3, R6.2
/LED_GR: IC1.26, R7.1
/LED_GR_R: D2.4, R7.2
/LED_RD: IC1.24, R5.1
/LED_RD_R: D2.1, R5.2
/MISO: IC1.2, P2.1
/MOSI: IC1.1, P2.4
/PWM00: IC1.33, S1.1
/PWM01: IC1.32, S1.2
/PWM02: IC1.31, S1.3
/PWM03: IC1.23, S2.1
/PWM04: IC1.22, S2.2
/PWM05: IC1.21, S2.3
/PWM06: IC1.41, S3.1
/PWM07: IC1.40, S3.2
/PWM08: IC1.34, S3.3
/PWM09: IC1.16, S4.1
/PWM10: IC1.15, S4.2
/PWM11: IC1.14, S4.3
/PWM12: IC1.44, S5.1
/PWM13: IC1.43, S5.2
/PWM14: IC1.42, S5.3
/PWM15: IC1.13, S6.1
/PWM16: IC1.12, S6.2
/PWM17: IC1.11, S6.3
/RESET: IC1.4, P2.5, R4.2
/SCK: IC1.3, P2.3
/SWITCHED_BATTERY: C1.1, C2.1, C5.1, D1.1, R2.1, S1.4, S1.5, S1.6, S2.4, S2.5, S2.6, S3.4, S3.5, S3.6, S4.4, S4.5, S4.6, S5.4, S5.5, S5.6, S6.4, S6.5, S6.6, SW1.3, SW1.6, VR1.2
/XTAL1: C9.2, IC1.8, X1.1
/XTAL2: C8.2, IC1.7, X1.2
GND: 1PIN.1, 1PIN#2.1, C1.2, C2.2, C3.2, C4.2, C5.2, C6.2, C8.1, C9.1, C10.1, D2.2, IC1.6, IC1.18, IC1.28, IC1.39, P1.2, P2.6, P3.1, P4.8, R1.2, R3.1, S1.7, S1.8, S1.9, S2.7, S2.8, S2.9, S3.7, S3.8, S3.9, S4.7, S4.8, S4.9, S5.7, S5.8, S5.9, S6.7, S6.8, S6.9, VR1.1, VR2.1, X1.3, ZD1.1, ZD2.1
unnamed: P3.5, R11.2
unnamed: P3.4, R9.2
unnamed: P3.3, SW2.2, SW2.5
unnamed: IC1.9, R8.1
unnamed: IC1.10, R10.1
unnamed: D1.2, R1.1
unnamed: P1.1, SW1.1, SW1.2, SW1.4, SW1.5
